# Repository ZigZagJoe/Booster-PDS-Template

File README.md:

# Macintosh 68030 PDS Template

This is a basic schematic and board layout for a card intended for use in a Macintosh SE/30 or IIsi PDS slot. It is based on a replica of the Interware Booster 50-SE30F board.

It is ideal for use in the IIsi and allows a second card to be used with a straight EuroDIN connector installed in CN2.

It may also be used in a SE/30 and allows stacking cards vertically. However, as it is a nonstandard formfactor, the chassis tabs will need to be carefully bent away and insulated from any second card installed.

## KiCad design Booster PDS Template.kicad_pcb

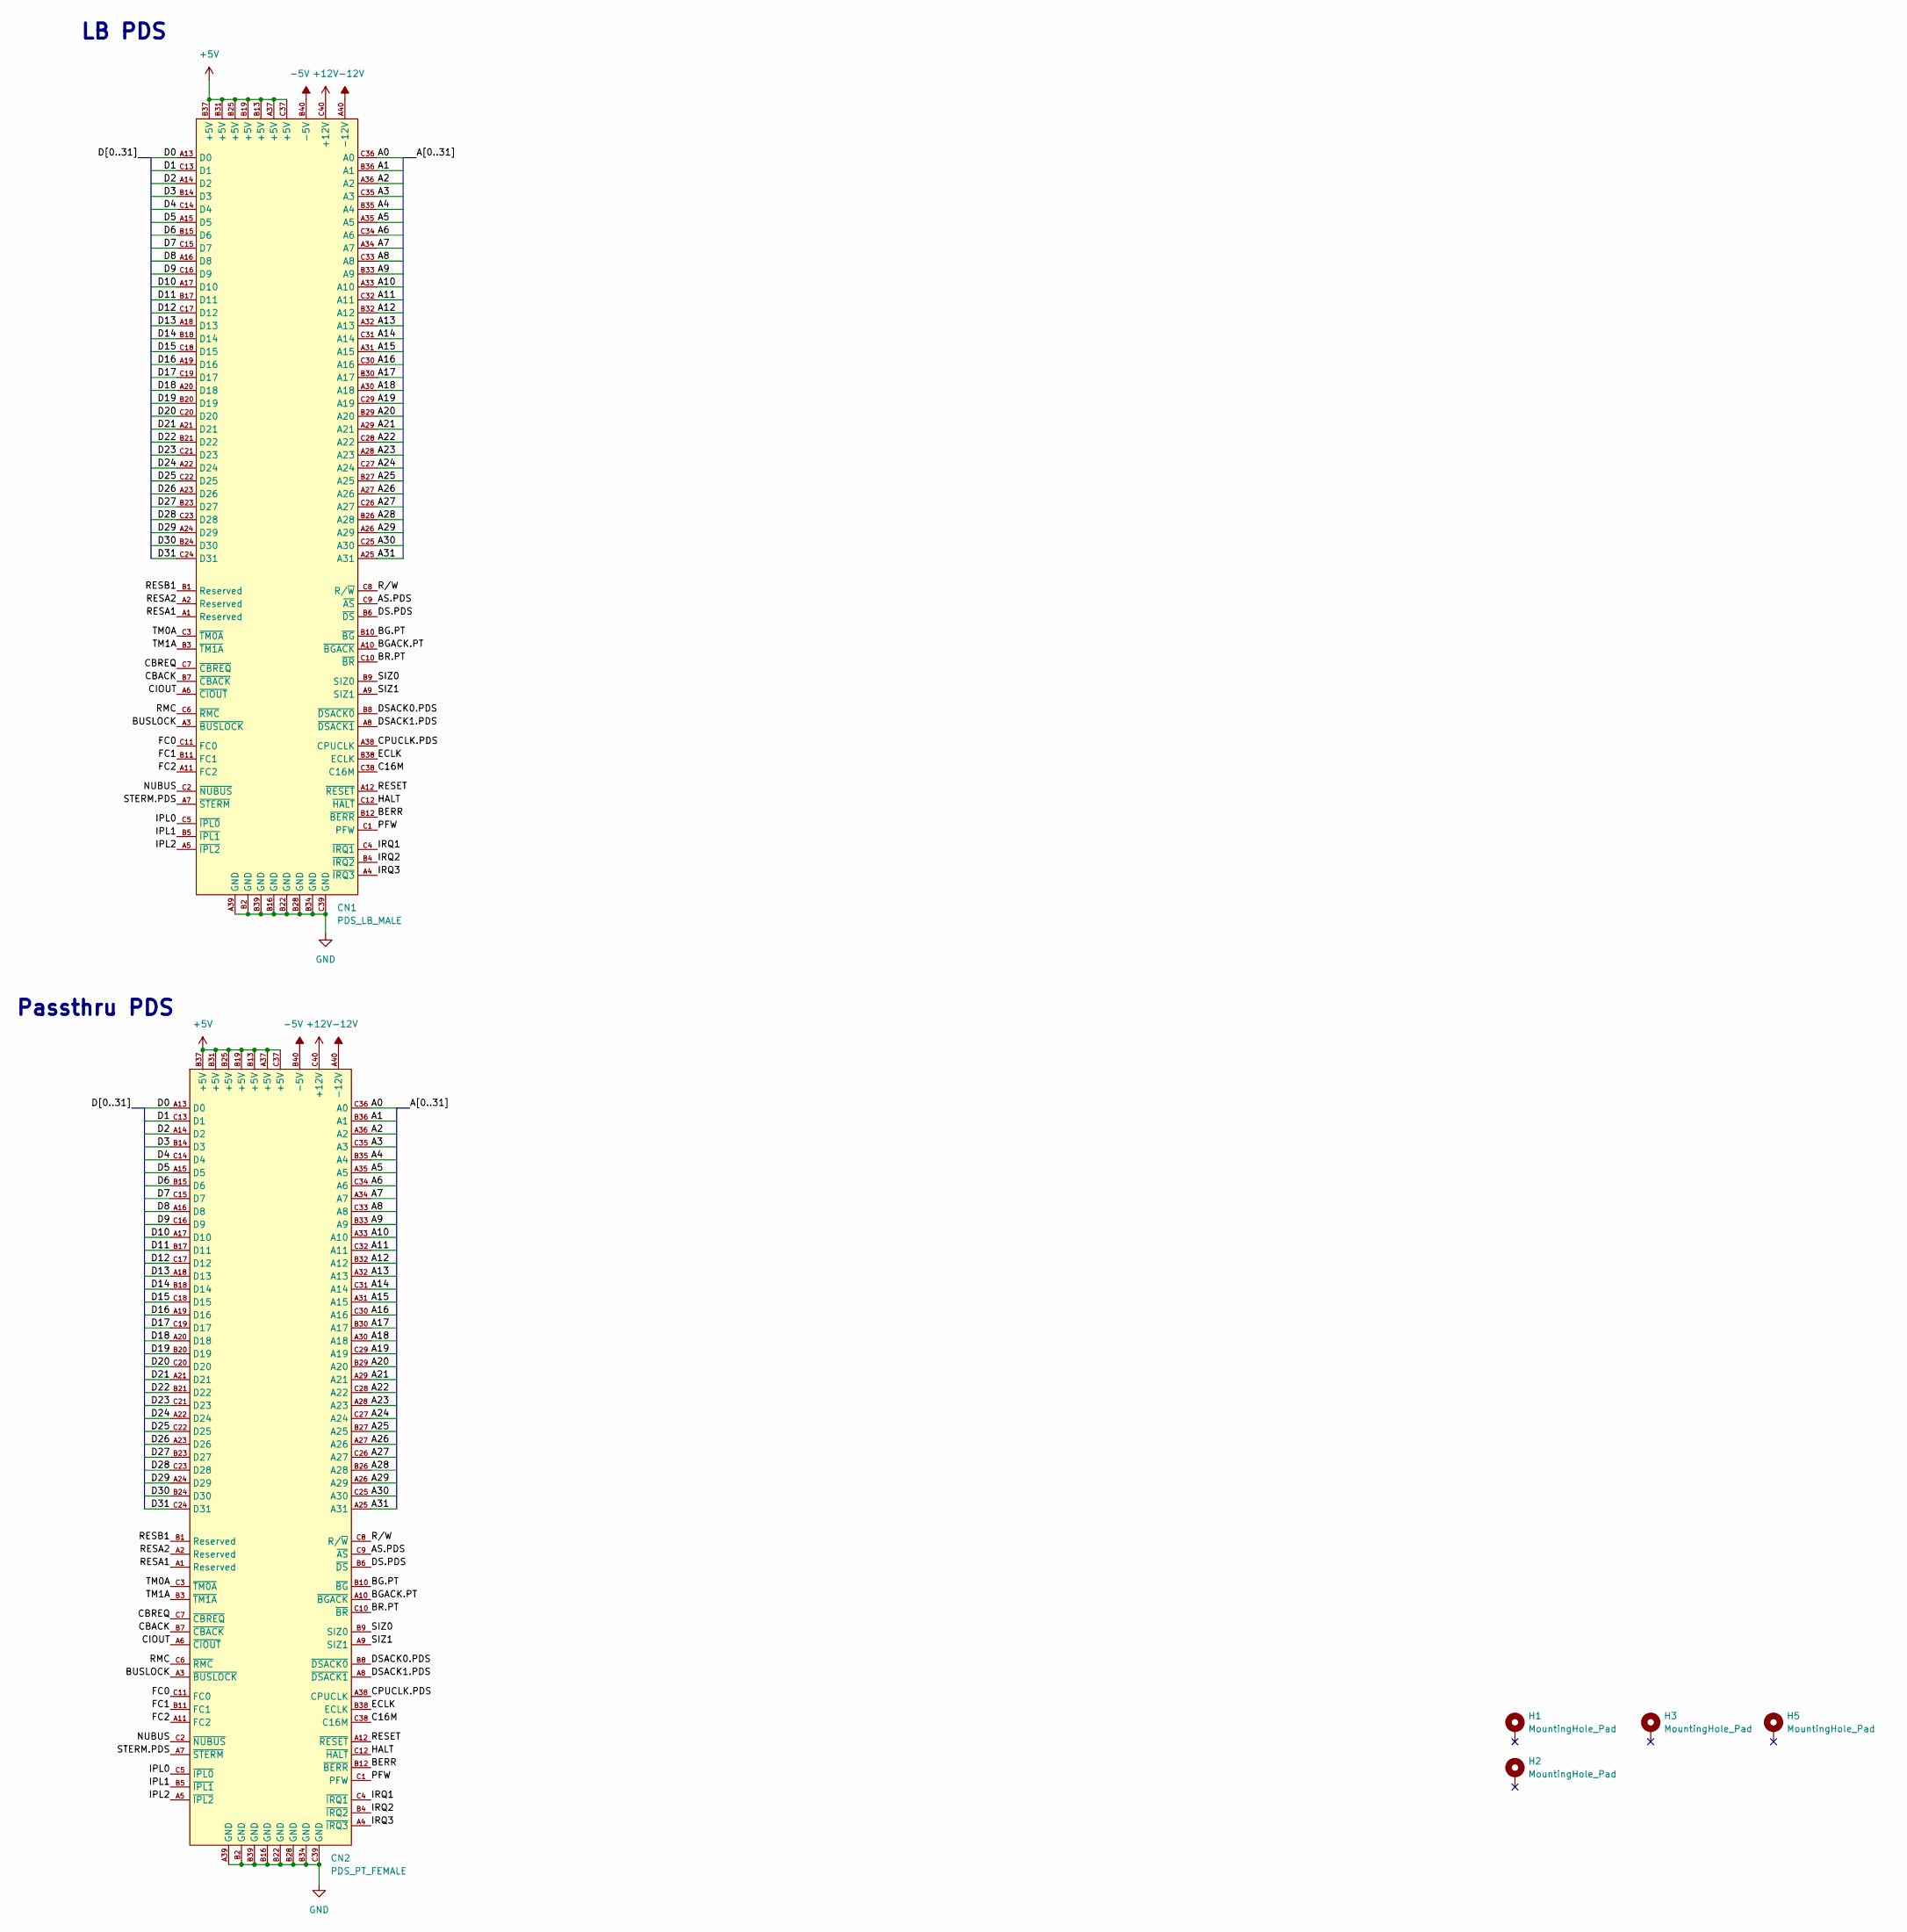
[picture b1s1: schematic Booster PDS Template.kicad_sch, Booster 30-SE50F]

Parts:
CN1: PDS_LB_MALE; IW_650949-5 RA MALE; Digikey A1277-ND
CN2: PDS_PT_FEMALE; IW_650874-4 RA FEMALE; Digikey A32307-ND
H1, H2, H3, H5: MountingHole_Pad; MountingHole_2.7mm_M2.5_DIN965_Pad; Digikey N/A

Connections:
+5V: CN1.A37 (+5V), CN1.B13 (+5V), CN1.B19 (+5V), CN1.B25 (+5V), CN1.B31 (+5V), CN1.B37 (+5V), CN1.C37 (+5V), CN2.A37 (+5V), CN2.B13 (+5V), CN2.B19 (+5V), CN2.B25 (+5V), CN2.B31 (+5V), CN2.B37 (+5V), CN2.C37 (+5V)
+12V: CN1.C40 (+12V), CN2.C40 (+12V)
-5V: CN1.B40 (-5V), CN2.B40 (-5V)
-12V: CN1.A40 (-12V), CN2.A40 (-12V)
/A0: CN1.C36 (A0), CN2.C36 (A0)
/A1: CN1.B36 (A1), CN2.B36 (A1)
/A2: CN1.A36 (A2), CN2.A36 (A2)
/A3: CN1.C35 (A3), CN2.C35 (A3)
/A4: CN1.B35 (A4), CN2.B35 (A4)
/A5: CN1.A35 (A5), CN2.A35 (A5)
/A6: CN1.C34 (A6), CN2.C34 (A6)
/A7: CN1.A34 (A7), CN2.A34 (A7)
/A8: CN1.C33 (A8), CN2.C33 (A8)
/A9: CN1.B33 (A9), CN2.B33 (A9)
/A10: CN1.A33 (A10), CN2.A33 (A10)
/A11: CN1.C32 (A11), CN2.C32 (A11)
/A12: CN1.B32 (A12), CN2.B32 (A12)
/A13: CN1.A32 (A13), CN2.A32 (A13)
/A14: CN1.C31 (A14), CN2.C31 (A14)
/A15: CN1.A31 (A15), CN2.A31 (A15)
/A16: CN1.C30 (A16), CN2.C30 (A16)
/A17: CN1.B30 (A17), CN2.B30 (A17)
/A18: CN1.A30 (A18), CN2.A30 (A18)
/A19: CN1.C29 (A19), CN2.C29 (A19)
/A20: CN1.B29 (A20), CN2.B29 (A20)
/A21: CN1.A29 (A21), CN2.A29 (A21)
/A22: CN1.C28 (A22), CN2.C28 (A22)
/A23: CN1.A28 (A23), CN2.A28 (A23)
/A24: CN1.C27 (A24), CN2.C27 (A24)
/A25: CN1.B27 (A25), CN2.B27 (A25)
/A26: CN1.A27 (A26), CN2.A27 (A26)
/A27: CN1.C26 (A27), CN2.C26 (A27)
/A28: CN1.B26 (A28), CN2.B26 (A28)
/A29: CN1.A26 (A29), CN2.A26 (A29)
/A30: CN1.C25 (A30), CN2.C25 (A30)
/A31: CN1.A25 (A31), CN2.A25 (A31)
/AS.PDS: CN1.C9 (~AS), CN2.C9 (~AS)
/BERR: CN1.B12 (~BERR), CN2.B12 (~BERR)
/BG.PT: CN1.B10 (~BG), CN2.B10 (~BG)
/BGACK.PT: CN1.A10 (~BGACK), CN2.A10 (~BGACK)
/BR.PT: CN1.C10 (~BR), CN2.C10 (~BR)
/BUSLOCK: CN1.A3 (~BUSLOCK), CN2.A3 (~BUSLOCK)
/C16M: CN1.C38 (C16M), CN2.C38 (C16M)
/CBACK: CN1.B7 (~CBACK), CN2.B7 (~CBACK)
/CBREQ: CN1.C7 (~CBREQ), CN2.C7 (~CBREQ)
/CIOUT: CN1.A6 (~CIOUT), CN2.A6 (~CIOUT)
/CPUCLK.PDS: CN1.A38 (CPUCLK), CN2.A38 (CPUCLK)
/D0: CN1.A13 (D0), CN2.A13 (D0)
/D1: CN1.C13 (D1), CN2.C13 (D1)
/D2: CN1.A14 (D2), CN2.A14 (D2)
/D3: CN1.B14 (D3), CN2.B14 (D3)
/D4: CN1.C14 (D4), CN2.C14 (D4)
/D5: CN1.A15 (D5), CN2.A15 (D5)
/D6: CN1.B15 (D6), CN2.B15 (D6)
/D7: CN1.C15 (D7), CN2.C15 (D7)
/D8: CN1.A16 (D8), CN2.A16 (D8)
/D9: CN1.C16 (D9), CN2.C16 (D9)
/D10: CN1.A17 (D10), CN2.A17 (D10)
/D11: CN1.B17 (D11), CN2.B17 (D11)
/D12: CN1.C17 (D12), CN2.C17 (D12)
/D13: CN1.A18 (D13), CN2.A18 (D13)
/D14: CN1.B18 (D14), CN2.B18 (D14)
/D15: CN1.C18 (D15), CN2.C18 (D15)
/D16: CN1.A19 (D16), CN2.A19 (D16)
/D17: CN1.C19 (D17), CN2.C19 (D17)
/D18: CN1.A20 (D18), CN2.A20 (D18)
/D19: CN1.B20 (D19), CN2.B20 (D19)
/D20: CN1.C20 (D20), CN2.C20 (D20)
/D21: CN1.A21 (D21), CN2.A21 (D21)
/D22: CN1.B21 (D22), CN2.B21 (D22)
/D23: CN1.C21 (D23), CN2.C21 (D23)
/D24: CN1.A22 (D24), CN2.A22 (D24)
/D25: CN1.C22 (D25), CN2.C22 (D25)
/D26: CN1.A23 (D26), CN2.A23 (D26)
/D27: CN1.B23 (D27), CN2.B23 (D27)
/D28: CN1.C23 (D28), CN2.C23 (D28)
/D29: CN1.A24 (D29), CN2.A24 (D29)
/D30: CN1.B24 (D30), CN2.B24 (D30)
/D31: CN1.C24 (D31), CN2.C24 (D31)
/DS.PDS: CN1.B6 (~DS), CN2.B6 (~DS)
/DSACK0.PDS: CN1.B8 (~DSACK0), CN2.B8 (~DSACK0)
/DSACK1.PDS: CN1.A8 (~DSACK1), CN2.A8 (~DSACK1)
/ECLK: CN1.B38 (ECLK), CN2.B38 (ECLK)
/FC0: CN1.C11 (FC0), CN2.C11 (FC0)
/FC1: CN1.B11 (FC1), CN2.B11 (FC1)
/FC2: CN1.A11 (FC2), CN2.A11 (FC2)
/HALT: CN1.C12 (~HALT), CN2.C12 (~HALT)
/IPL0: CN1.C5 (~IPL0), CN2.C5 (~IPL0)
/IPL1: CN1.B5 (~IPL1), CN2.B5 (~IPL1)
/IPL2: CN1.A5 (~IPL2), CN2.A5 (~IPL2)
/IRQ1: CN1.C4 (~IRQ1), CN2.C4 (~IRQ1)
/IRQ2: CN1.B4 (~IRQ2), CN2.B4 (~IRQ2)
/IRQ3: CN1.A4 (~IRQ3), CN2.A4 (~IRQ3)
/NUBUS: CN1.C2 (~NUBUS), CN2.C2 (~NUBUS)
/PFW: CN1.C1 (PFW), CN2.C1 (PFW)
/RESA1: CN1.A1 (Reserved), CN2.A1 (Reserved)
/RESA2: CN1.A2 (Reserved), CN2.A2 (Reserved)
/RESB1: CN1.B1 (Reserved), CN2.B1 (Reserved)
/RESET: CN1.A12 (~RESET), CN2.A12 (~RESET)
/RMC: CN1.C6 (~RMC), CN2.C6 (~RMC)
/R/W: CN1.C8 (R/~W), CN2.C8 (R/~W)
/SIZ0: CN1.B9 (SIZ0), CN2.B9 (SIZ0)
/SIZ1: CN1.A9 (SIZ1), CN2.A9 (SIZ1)
/STERM.PDS: CN1.A7 (~STERM), CN2.A7 (~STERM)
/TM0A: CN1.C3 (~TM0A), CN2.C3 (~TM0A)
/TM1A: CN1.B3 (~TM1A), CN2.B3 (~TM1A)
GND: CN1.A39 (GND), CN1.B2 (GND), CN1.B16 (GND), CN1.B22 (GND), CN1.B28 (GND), CN1.B34 (GND), CN1.B39 (GND), CN1.C39 (GND), CN2.A39 (GND), CN2.B2 (GND), CN2.B16 (GND), CN2.B22 (GND), CN2.B28 (GND), CN2.B34 (GND), CN2.B39 (GND), CN2.C39 (GND)

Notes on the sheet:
Passthru PDS
LB PDS

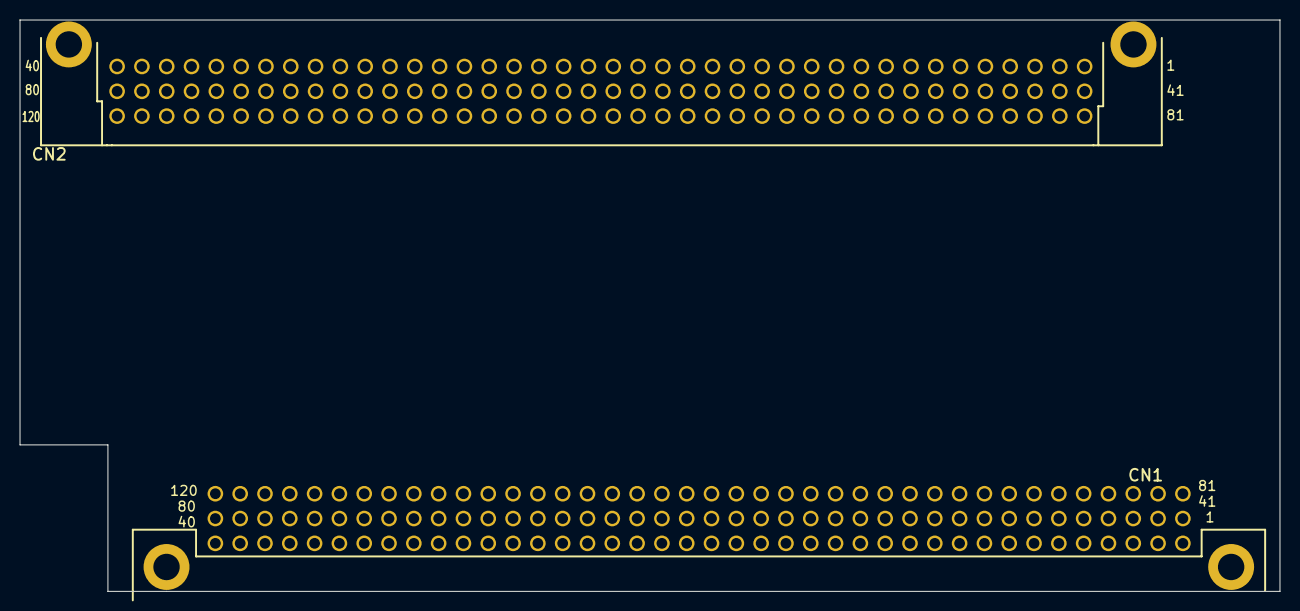
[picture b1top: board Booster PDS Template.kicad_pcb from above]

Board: 4 copper layers, 129.0 x 58.5 mm, 6 parts (0 on the bottom side), 107 nets.
